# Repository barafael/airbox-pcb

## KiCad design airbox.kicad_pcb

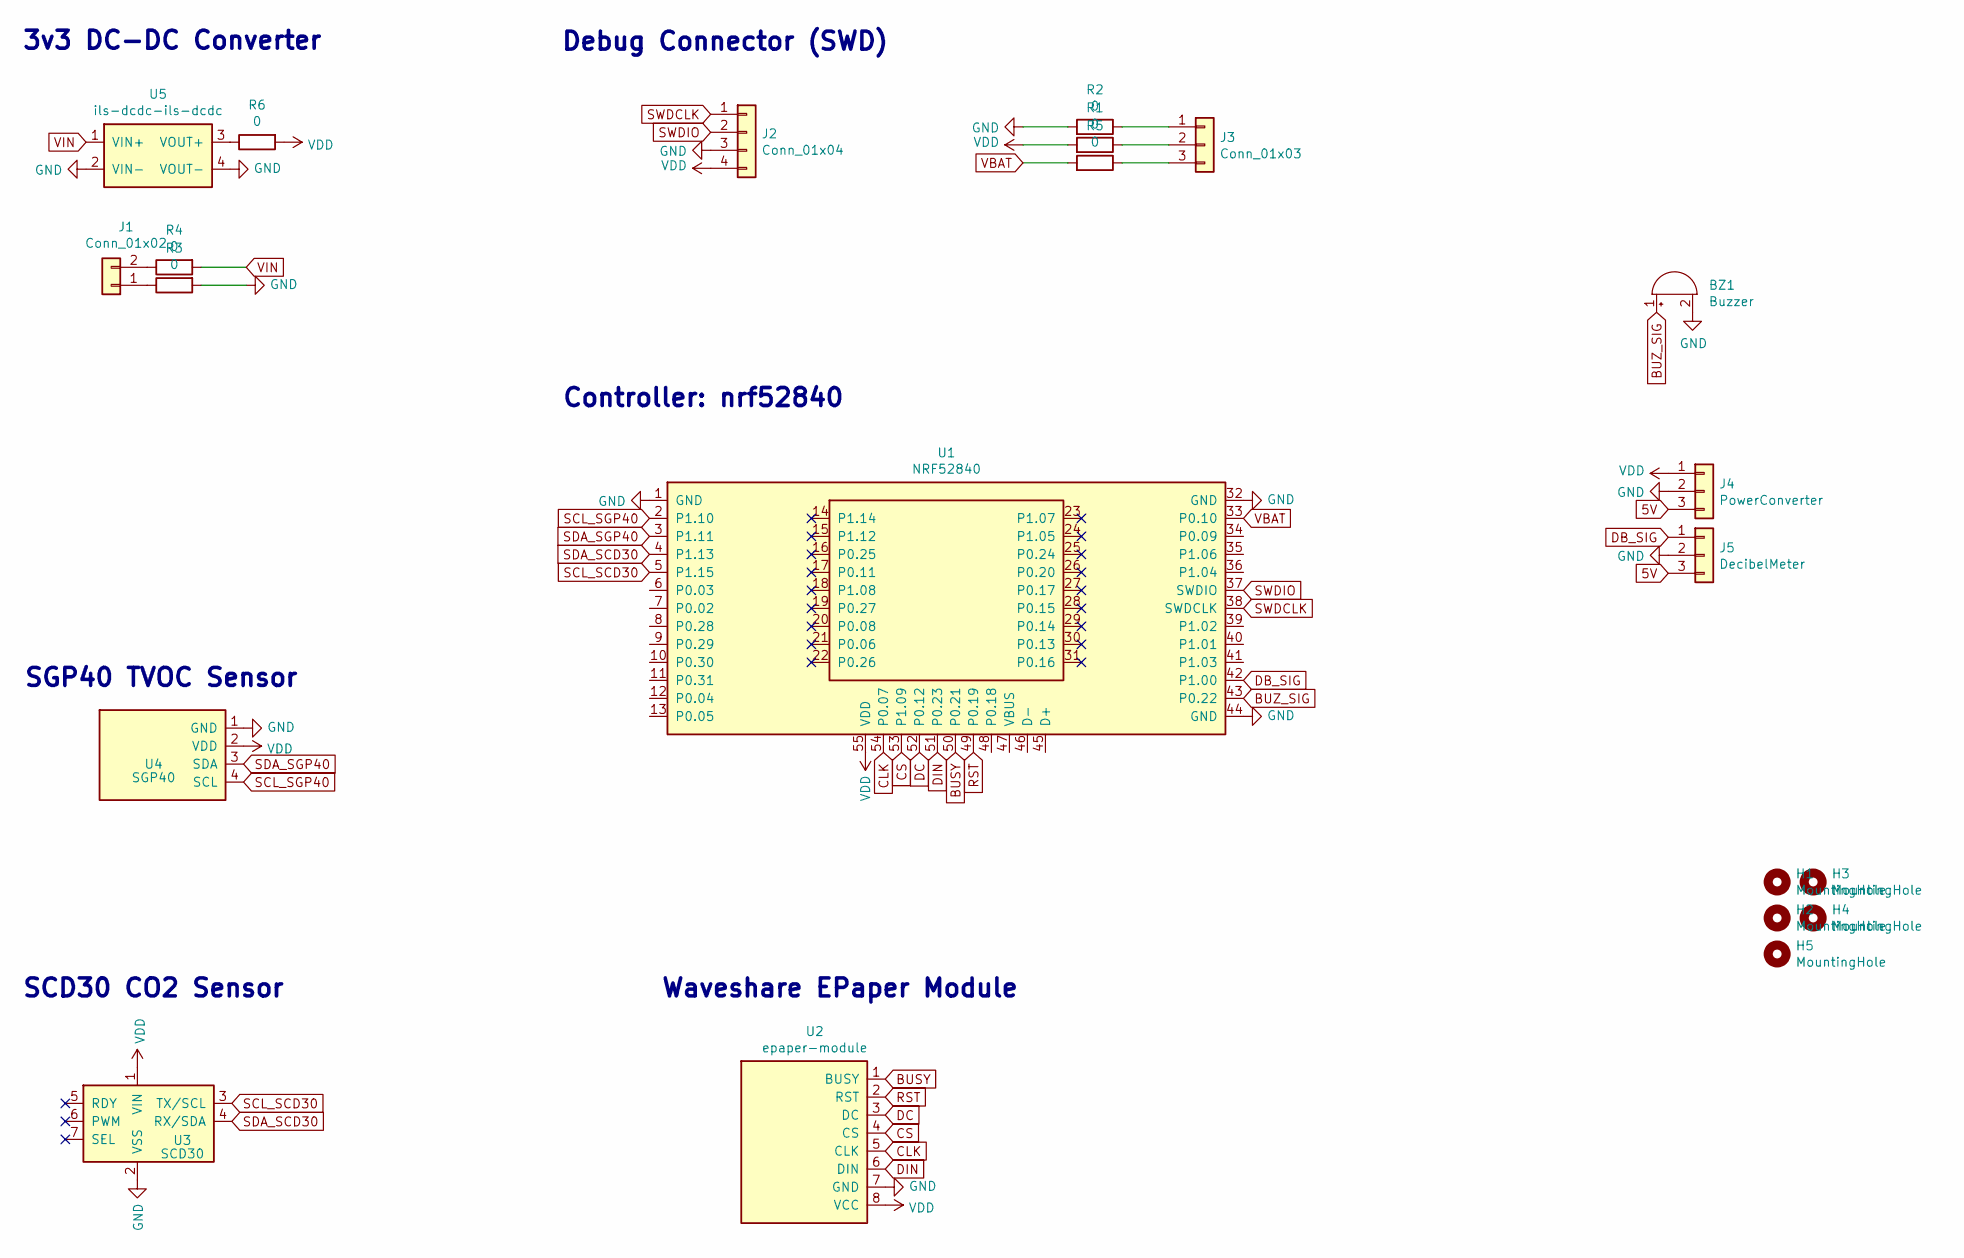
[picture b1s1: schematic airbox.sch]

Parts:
BZ1: Buzzer; PS1240P02BT
H1, H2, H3, H4, H5: MountingHole; MountingHole_3mm
J1: Conn_01x02; JST_EH_B2B-EH-A_1x02_P2.50mm_Vertical
J2: Conn_01x04; JST_EH_B4B-EH-A_1x04_P2.50mm_Vertical
J3: Conn_01x03; JST_EH_B3B-EH-A_1x03_P2.50mm_Vertical
J4: PowerConverter; PinSocket_1x03_P2.54mm_Vertical
J5: DecibelMeter; PinSocket_1x03_P2.54mm_Vertical
R1, R2, R3, R4, R5, R6: 0; R_0805_2012Metric
U1: NRF52840; nrf52-waveshare
U2: epaper-module
U3: SCD30; scd30
U4: SGP40; sgp40-sparkx-breakout
U5: ils-dcdc-ils-dcdc; ils-3v3dcdc

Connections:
5V: J4.3, J5.3
BUSY: U1.50 (P0.21), U2.1 (BUSY)
BUZ_SIG: BZ1.1 (-), U1.43 (P0.22)
CLK: U1.54 (P0.07), U2.5 (CLK)
CS: U1.53 (P1.09), U2.4 (CS)
DB_SIG: J5.1, U1.42 (P1.00)
DC: U1.52 (P0.12), U2.3 (DC)
DIN: U1.51 (P0.23), U2.6 (DIN)
GND: BZ1.2 (+), J2.3, J4.2, J5.2, R2.2, R3.2, U1.1 (GND), U1.32 (GND), U1.44 (GND), U2.7 (GND), U3.2 (VSS), U4.1 (GND), U5.2 (VIN-), U5.4 (VOUT-)
unnamed: J1.1, R3.1
unnamed: J1.2, R4.1
unnamed: J3.1, R2.1
unnamed: J3.2, R1.1
unnamed: J3.3, R5.1
unnamed: R6.1, U5.3 (VOUT+)
RST: U1.49 (P0.19), U2.2 (RST)
SCL_SCD30: U1.5 (P1.15), U3.3 (TX/SCL)
SCL_SGP40: U1.2 (P1.10), U4.4 (SCL)
SDA_SCD30: U1.4 (P1.13), U3.4 (RX/SDA)
SDA_SGP40: U1.3 (P1.11), U4.3 (SDA)
SWDCLK: J2.1, U1.38 (SWDCLK)
SWDIO: J2.2, U1.37 (SWDIO)
VBAT: R5.2, U1.33 (P0.10)
VDD: J2.4, J4.1, R1.2, R6.2, U1.55 (VDD), U2.8 (VCC), U3.1 (VIN), U4.2 (VDD)
VIN: R4.2, U5.1 (VIN+)

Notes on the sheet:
Controller: nrf52840
Debug Connector (SWD)
3v3 DC-DC Converter
SGP40 TVOC Sensor
SCD30 CO2 Sensor
Waveshare EPaper Module

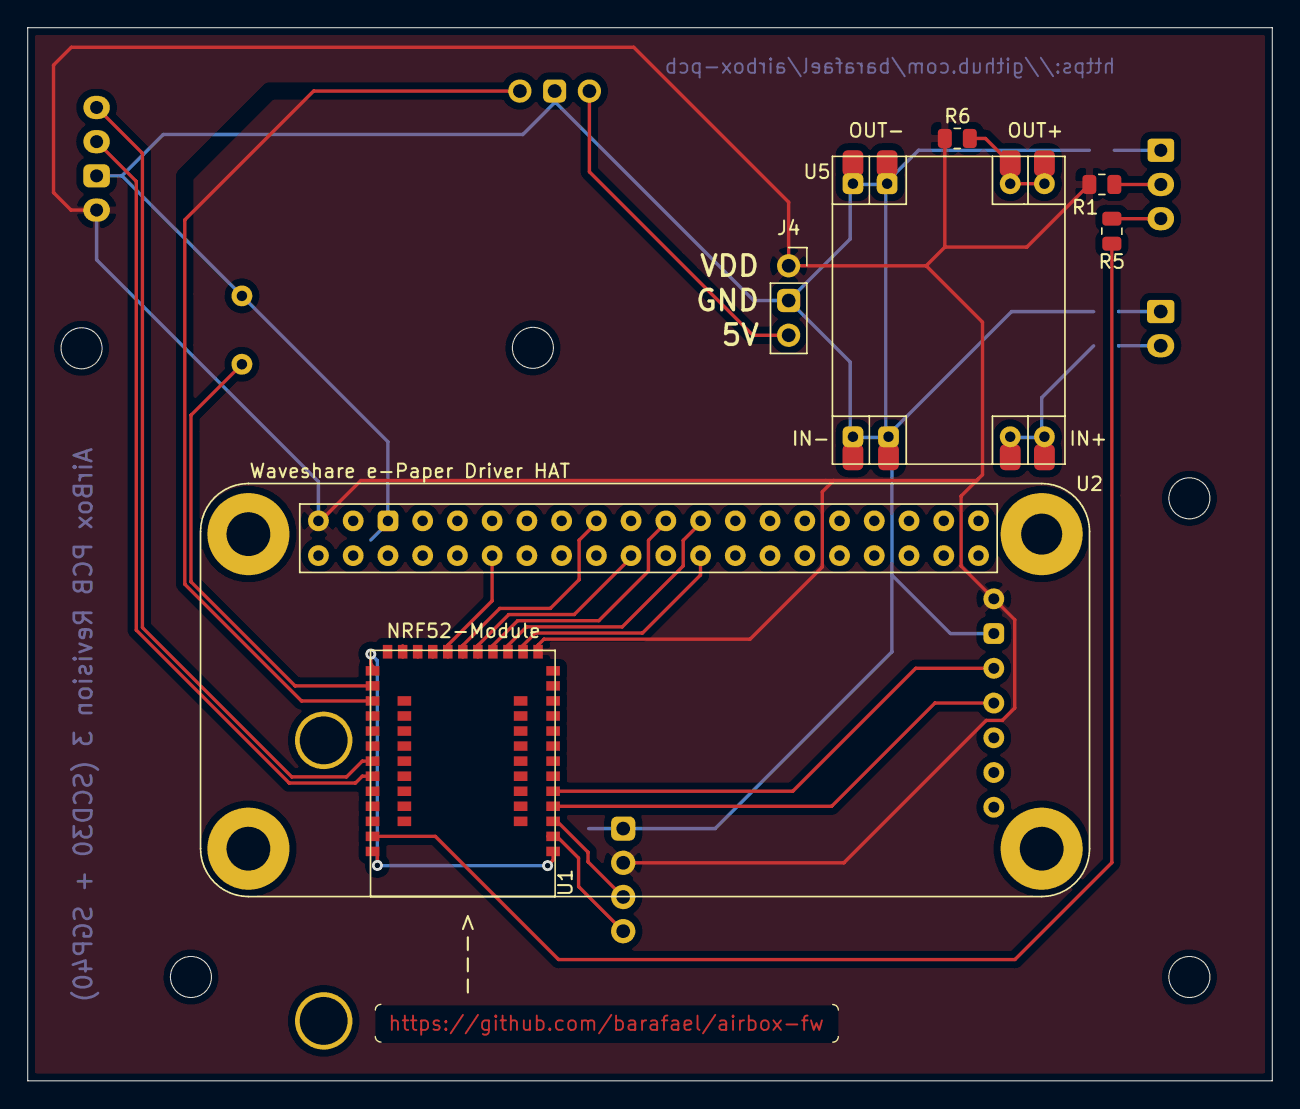
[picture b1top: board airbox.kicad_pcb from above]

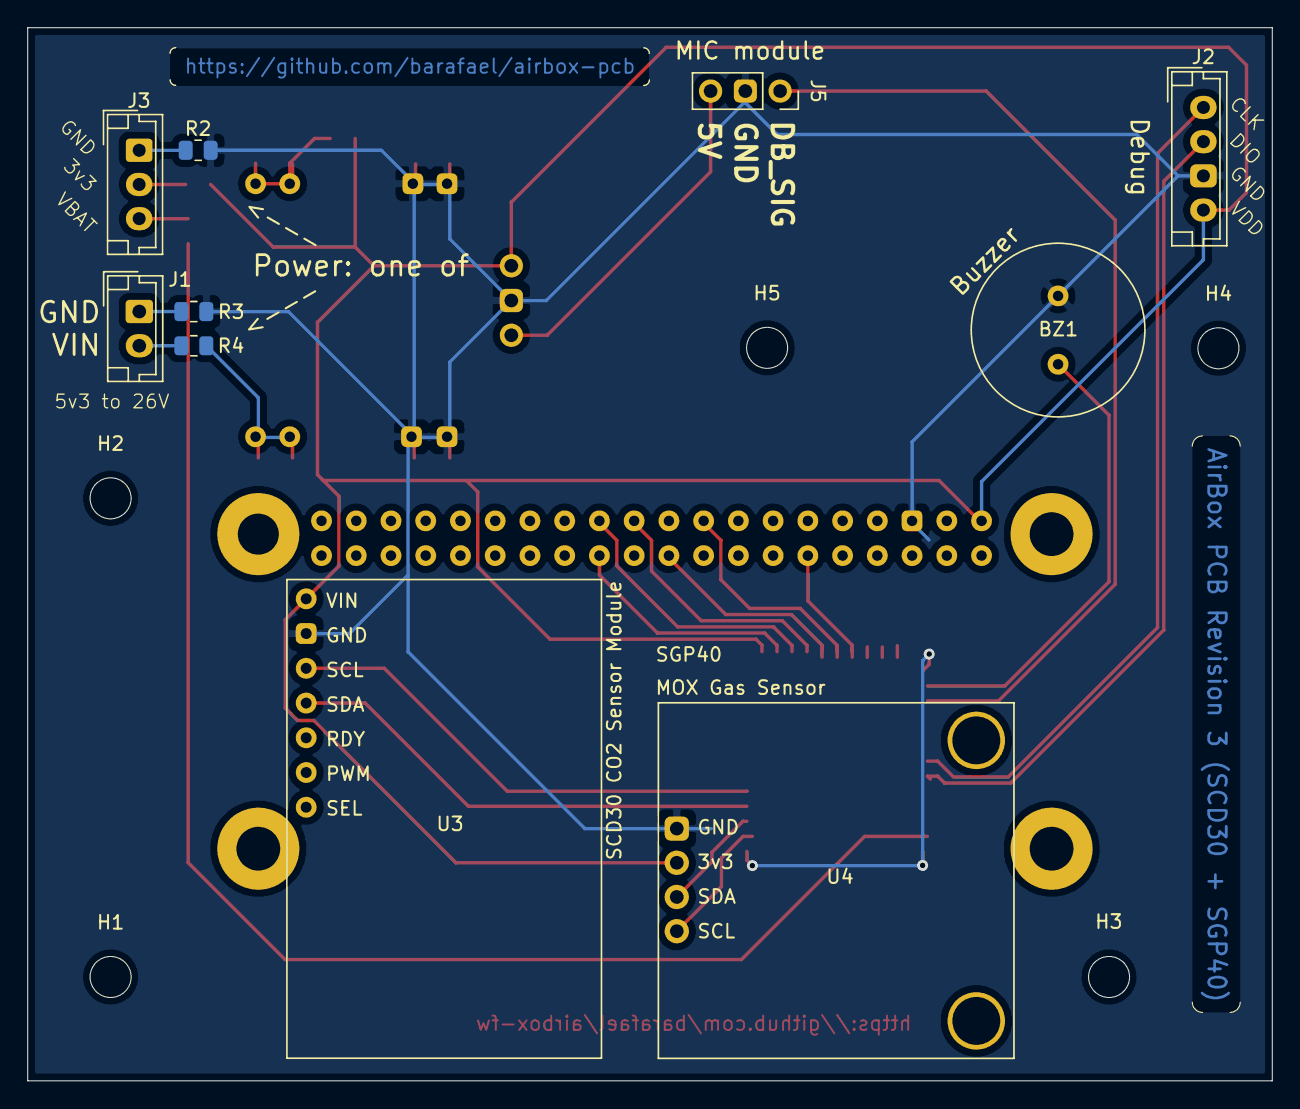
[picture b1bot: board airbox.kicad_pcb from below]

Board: 2 copper layers, 91.0 x 77.0 mm, 22 parts (10 on the bottom side), 25 nets.

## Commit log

2021-03-12 Add cache lib
2021-03-13 Add tables
2021-03-16 Add sgp40 submodule
2021-03-16 Add sgp40
2021-03-21 Update submodules
2021-03-22 Add DCDC for power
2021-03-22 Improve labels on PCB
2021-03-22 More improve labels
2021-03-25 Rework PCB
2021-03-25 Add buzzer footprint
2021-03-25 Board revision 1
2021-03-25 Finishing touches
2021-04-11 Update board and submodules
2021-04-11 Add board render to readme
2021-04-14 Add board renders
2021-04-28 Make .gitmodules not use ssh again
2021-04-28 Minor adjustments
2021-06-13 Fix paths and relax track distances a little
